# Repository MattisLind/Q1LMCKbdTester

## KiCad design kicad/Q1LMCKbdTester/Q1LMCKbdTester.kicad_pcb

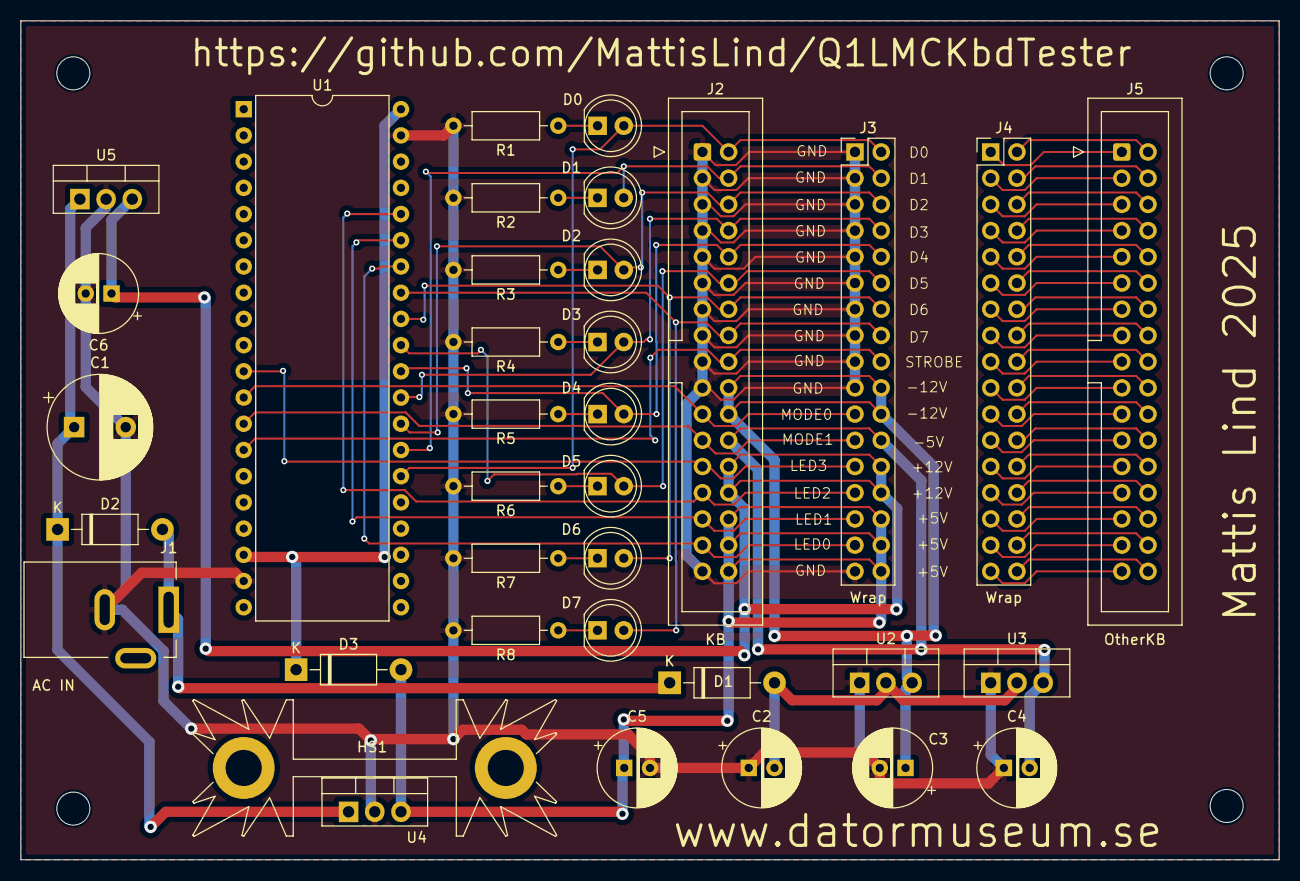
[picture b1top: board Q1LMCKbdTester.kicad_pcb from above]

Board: 2 copper layers, 121.9 x 81.3 mm, 40 parts (0 on the bottom side), 66 nets.

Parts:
C1: 1000u 25V; CP_Radial_D10.0mm_P5.00mm
C2, C3, C4, C5, C6: 100u 25V; CP_Radial_D7.5mm_P2.50mm
D1, D2: 1N4004; D_DO-41_SOD81_P10.16mm_Horizontal
D3: Schottky; D_DO-41_SOD81_P10.16mm_Horizontal
D4: D0; LED_D5.0mm
D5: D1; LED_D5.0mm
D6: D2; LED_D5.0mm
D7: D3; LED_D5.0mm
D8: D4; LED_D5.0mm
D9: D5; LED_D5.0mm
D10: D6; LED_D5.0mm
D11: D7; LED_D5.0mm
H1, H2, H3, H4: MountingHole; MountingHole_3.2mm_M3_DIN965
HS1: Heatsink_Pad_2Pin; Heatsink_Fischer_SK104-STCB_35x13mm__2xDrill3.5mm_ScrewM3
J1: AC IN; BarrelJack_Kycon_KLDX-0202-xC_Horizontal
J2: KB; IDC-Header_2x17_P2.54mm_Vertical
J3, J4: Wrap; PinHeader_2x17_P2.54mm_Vertical
J5: OtherKB; IDC-Header_2x17_P2.54mm_Vertical
R1, R2, R3, R4, R5, R6, R7, R8: 1k; R_Axial_DIN0207_L6.3mm_D2.5mm_P10.16mm_Horizontal
U1: STM32F411 BlackPill; DIP-40_W15.24mm
U2: L7912; TO-220-3_Vertical
U3: L7905; TO-220-3_Vertical
U4: L7805; TO-220-3_Vertical
U5: L7812; TO-220-3_Vertical

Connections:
+5V: C5.1, D3.2 (A), J2.30, J2.32, J2.34, J3.30, J3.32, J3.34, U4.3 (OUT)
+12V: C6.1, J2.26, J2.28, J3.26, J3.28, U5.3 (OUT)
-5V: C4.2, J2.24, J3.24, U3.3 (VO)
-12V: C3.1, J2.20, J2.22, J3.20, J3.22, U2.3 (VO)
/D0: D4.2 (A), J2.2, J3.2, U1.26 (PA0)
/D1: D5.2 (A), J2.4, J3.4, U1.27 (PA1)
/D2: D6.2 (A), J2.6, J3.6, U1.28 (PA2)
/D3: D7.2 (A), J2.8, J3.8, U1.29 (PA3)
/D4: D8.2 (A), J2.10, J3.10, U1.30 (PA4)
/D5: D9.2 (A), J2.12, J3.12, U1.31 (PA5)
/D6: D10.2 (A), J2.14, J3.14, U1.32 (PA6)
/D7: D11.2 (A), J2.16, J3.16, U1.33 (PA7)
/LED0: J2.31, J3.31, U1.34 (PB0)
/LED1: J2.29, J3.29, U1.35 (PB1)
/LED2: J2.27, J3.27, U1.36 (PB2)
/LED3: J2.25, J3.25, U1.11 (PB3)
/MODE0: J2.21, J3.21, U1.12 (PB4)
/MODE1: J2.23, J3.23, U1.13 (PB5)
/STROBE: J2.18, J3.18, U1.14 (PB6)
GND: C1.2, C2.1, C3.2, C4.1, C5.2, C6.2, J1.2, J2.1, J2.3, J2.5, J2.7, J2.9, J2.11, J2.13, J2.15, J2.17, J2.19, J2.33, J3.1, J3.3, J3.5, J3.7, J3.9, J3.11, J3.13, J3.15, J3.17, J3.19, J3.33, R1.2, R2.2, R3.2, R4.2, R5.2, R6.2, R7.2, R8.2, U1.19 (GND), U1.39 (GND), U2.1 (GND), U3.1 (GND), U4.2 (GND), U5.2 (GND)
unnamed: C2.2, D1.2 (A), U2.2 (VI), U3.2 (VI)
unnamed: D1.1 (K), D2.2 (A), J1.1
unnamed: C1.1, D2.1 (K), U4.1 (IN), U5.1 (IN)
unnamed: D3.1 (K), U1.18 (5V), U1.40 (+5V)
unnamed: D4.1 (K), R1.1
unnamed: D5.1 (K), R2.1
unnamed: D6.1 (K), R3.1
unnamed: D7.1 (K), R4.1
unnamed: D8.1 (K), R5.1
unnamed: D9.1 (K), R6.1
unnamed: D10.1 (K), R7.1
unnamed: D11.1 (K), R8.1
unnamed: J4.1, J5.1
unnamed: J4.2, J5.2
unnamed: J4.3, J5.3
unnamed: J4.4, J5.4
unnamed: J4.5, J5.5
unnamed: J4.6, J5.6
unnamed: J4.7, J5.7
unnamed: J4.8, J5.8
unnamed: J4.9, J5.9
unnamed: J4.10, J5.10
unnamed: J4.11, J5.11
unnamed: J4.12, J5.12
unnamed: J4.13, J5.13
unnamed: J4.14, J5.14
unnamed: J4.15, J5.15
unnamed: J4.16, J5.16
unnamed: J4.17, J5.17
unnamed: J4.18, J5.18
unnamed: J4.19, J5.19
unnamed: J4.20, J5.20
unnamed: J4.21, J5.21
unnamed: J4.22, J5.22
unnamed: J4.23, J5.23
unnamed: J4.24, J5.24
unnamed: J4.25, J5.25
unnamed: J4.26, J5.26
unnamed: J4.27, J5.27
unnamed: J4.28, J5.28
unnamed: J4.29, J5.29
unnamed: J4.30, J5.30
unnamed: J4.31, J5.31
unnamed: J4.32, J5.32
unnamed: J4.33, J5.33
unnamed: J4.34, J5.34

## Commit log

2025-02-15 Initial commit of schematic
2025-02-18 Now sent to jlcpcb..
